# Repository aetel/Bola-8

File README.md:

# Bola-8

Project made for sfera 2018 by victor bernardos and lukilukeskywalker
<ul>
  The Bola 8, or more commonly known Magic ball 8, is a project based on the hackaday posted <a href="https://hackaday.com/2018/04/05/magic-8-ball-business-card-will-answer-all-your-questions/">project</a>
  It works by having a tilt sensor conected to the clock input of a decade counter. Each output of the decade counter is conected to an led, that neben it has a text that predicts your future.
  The project can be edited to have your own personalized predictions (Just go to the pcbEditor of Kicad, and change the values of the text).
  </ul>
  <h2>Componets BOM</h2>
  <li><a href="https://de.aliexpress.com/item/100PCS-LOT-SW-200D-Ball-Switch-SW-200D-Tilt-Angle-Sensor-Switch-Angle-Switch-Transducer/32757296355.html?spm=a2g0s.9042311.0.0.27424c4dg2IXFF">Tilt sensor</a> </li>
  <li>8 Leds 1206 SMD</li>
  <li>1 10 kOhm and 1 220 Ohm 1206 SMD resistors </li>
  <li><a href="https://www.mouser.es/ProductDetail/595-CD74HC4017NSR">74HC4017</a> </li>
  <li><a href="https://www.mouser.com/ProductDetail/688-SKQGAKE010">One Push Button</a> </li>
  <li><a href="https://www.mouser.com/ProductDetail/712-BAT-HLD-001">Button Battery Holder</a> </li>

And of course, the leds are separated at the same distance (for those who have OCD ;))
To make it work, just press the button, and move the Bola 8 up and down, while you make a question

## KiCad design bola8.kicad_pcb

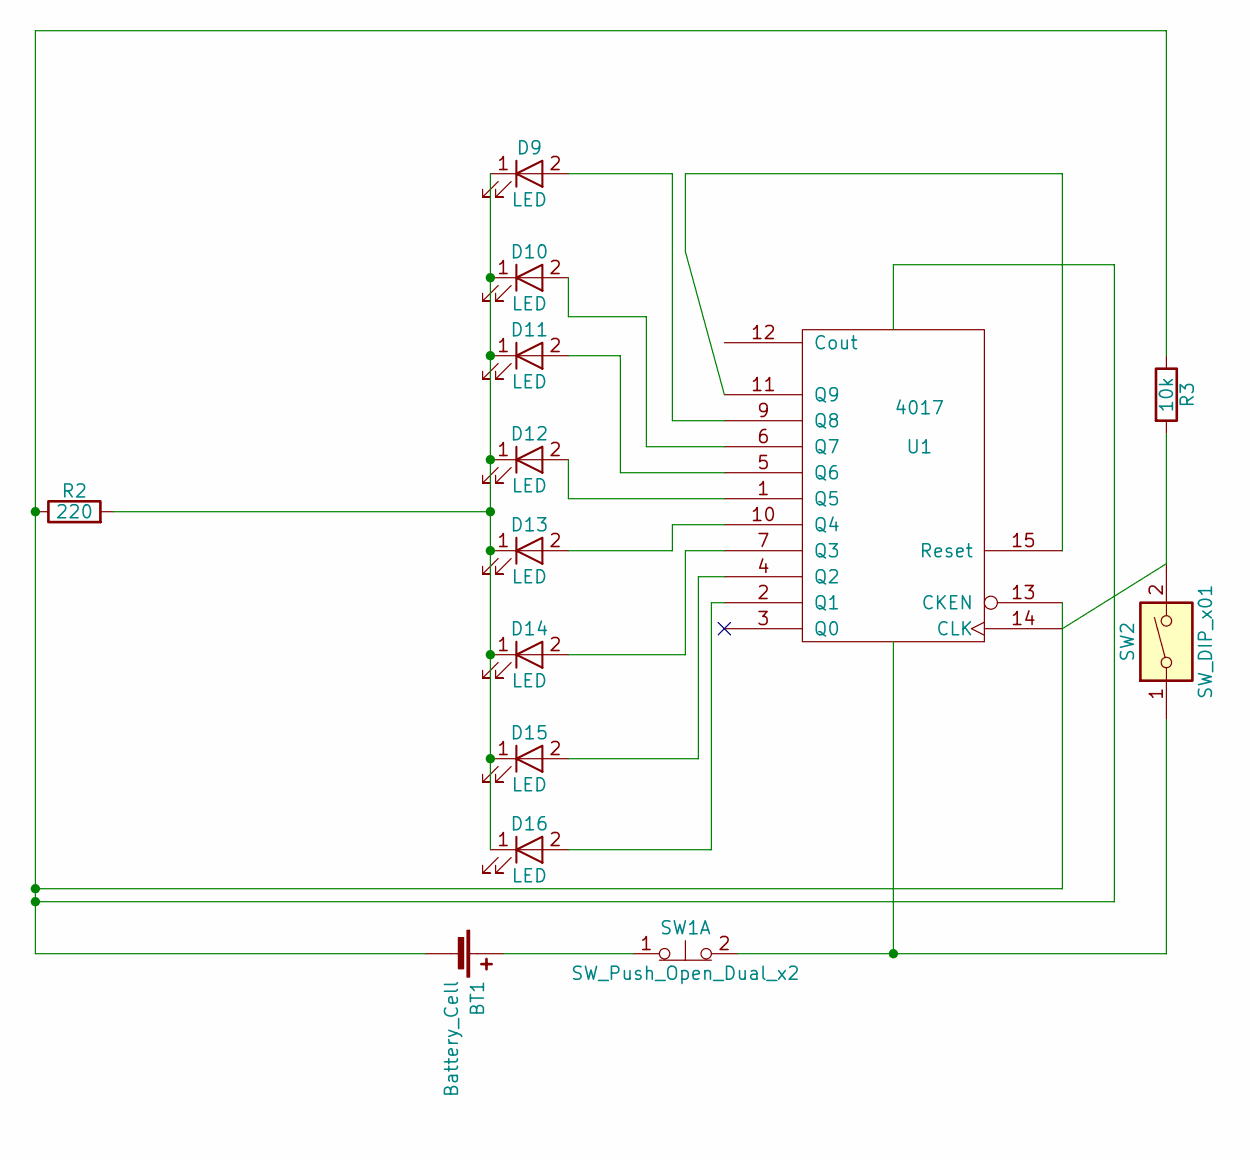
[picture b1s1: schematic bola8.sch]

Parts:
BT1: Battery_Cell; LINX CR2032 Holder
D9, D10, D11, D12, D13, D14, D15, D16: LED; LED_1206_HandSoldering
R2: 220; R_1206_HandSoldering
R3: 10k; R_1206_HandSoldering
SW1: SW_Push_Open_Dual_x2; SW_SPST_SKQG
SW2: SW_DIP_x01; R_Axial_DIN0309_L9.0mm_D3.2mm_P15.24mm_Horizontal
U1: 4017; SOP-16_4.4x10.4mm_Pitch1.27mm

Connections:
unnamed: BT1.1 (+), SW1.1
unnamed: D9.2 (A), U1.9 (Q8)
unnamed: D9.1 (K), D10.1 (K), D11.1 (K), D12.1 (K), D13.1 (K), D14.1 (K), D15.1 (K), D16.1 (K), R2.2
unnamed: D10.2 (A), U1.6 (Q7)
unnamed: D11.2 (A), U1.5 (Q6)
unnamed: D12.2 (A), U1.1 (Q5)
unnamed: D13.2 (A), U1.10 (Q4)
unnamed: D14.2 (A), U1.7 (Q3)
unnamed: D15.2 (A), U1.4 (Q2)
unnamed: D16.2 (A), U1.2 (Q1)
unnamed: R3.2, SW2.2, U1.14 (CLK)
unnamed: U1.11 (Q9), U1.15 (Reset)
VDD: SW1.2, SW2.1, U1.16 (VDD)
VSS: BT1.2 (-), R2.1, R3.1, U1.8 (VSS), U1.13 (CKEN)

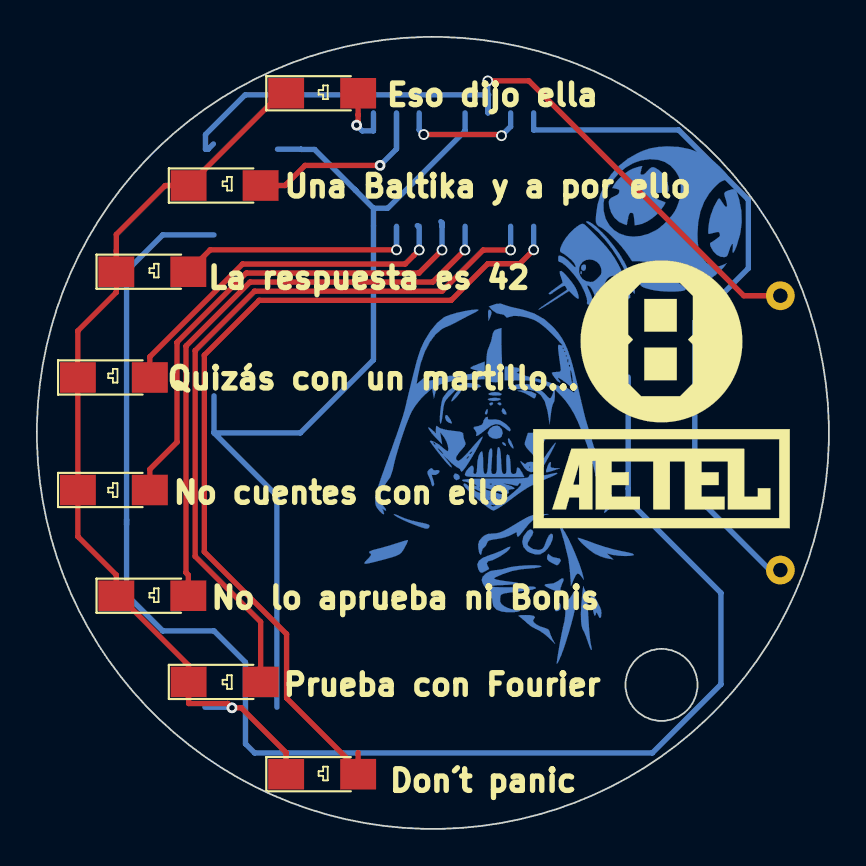
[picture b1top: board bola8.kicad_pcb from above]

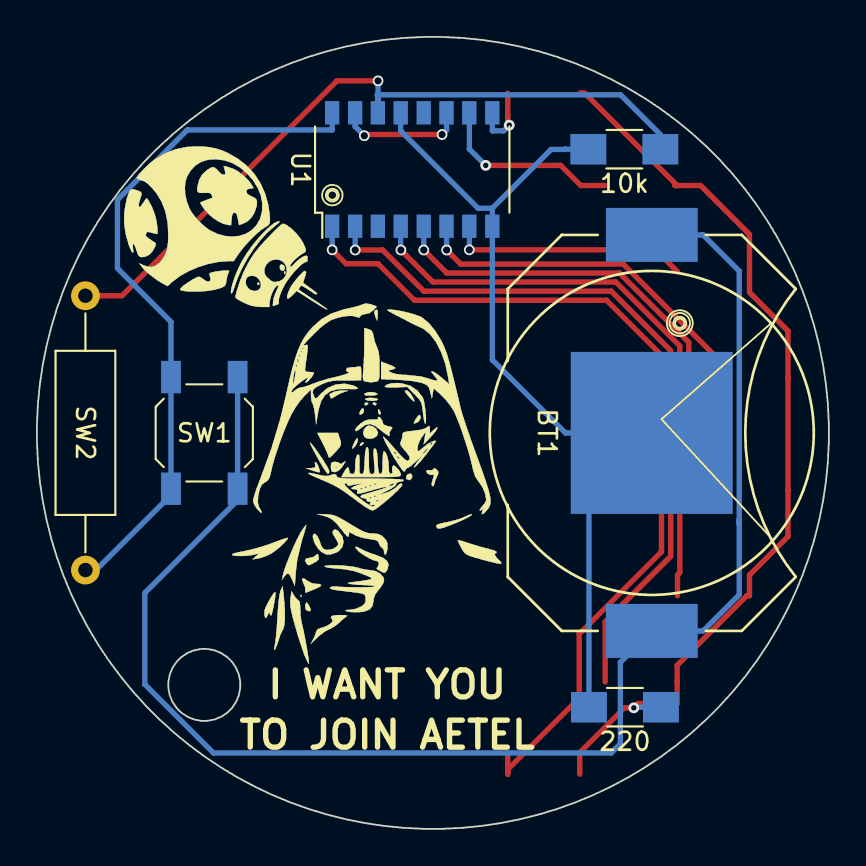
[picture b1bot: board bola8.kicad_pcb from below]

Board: 2 copper layers, 44.0 x 44.0 mm, 17 parts (7 on the bottom side), 14 nets.

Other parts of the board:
AETEL: LOGO; 753
Bola 8: LOGO; 123
Darth: LOGO; Darth Vader

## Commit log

2019-01-27 Added Gerbers and 3d MODELS
